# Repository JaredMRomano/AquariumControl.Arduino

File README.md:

# Aquarium Controller

Aquarium Controller a reef controller using Arduino and eventually Raspberri-Pi

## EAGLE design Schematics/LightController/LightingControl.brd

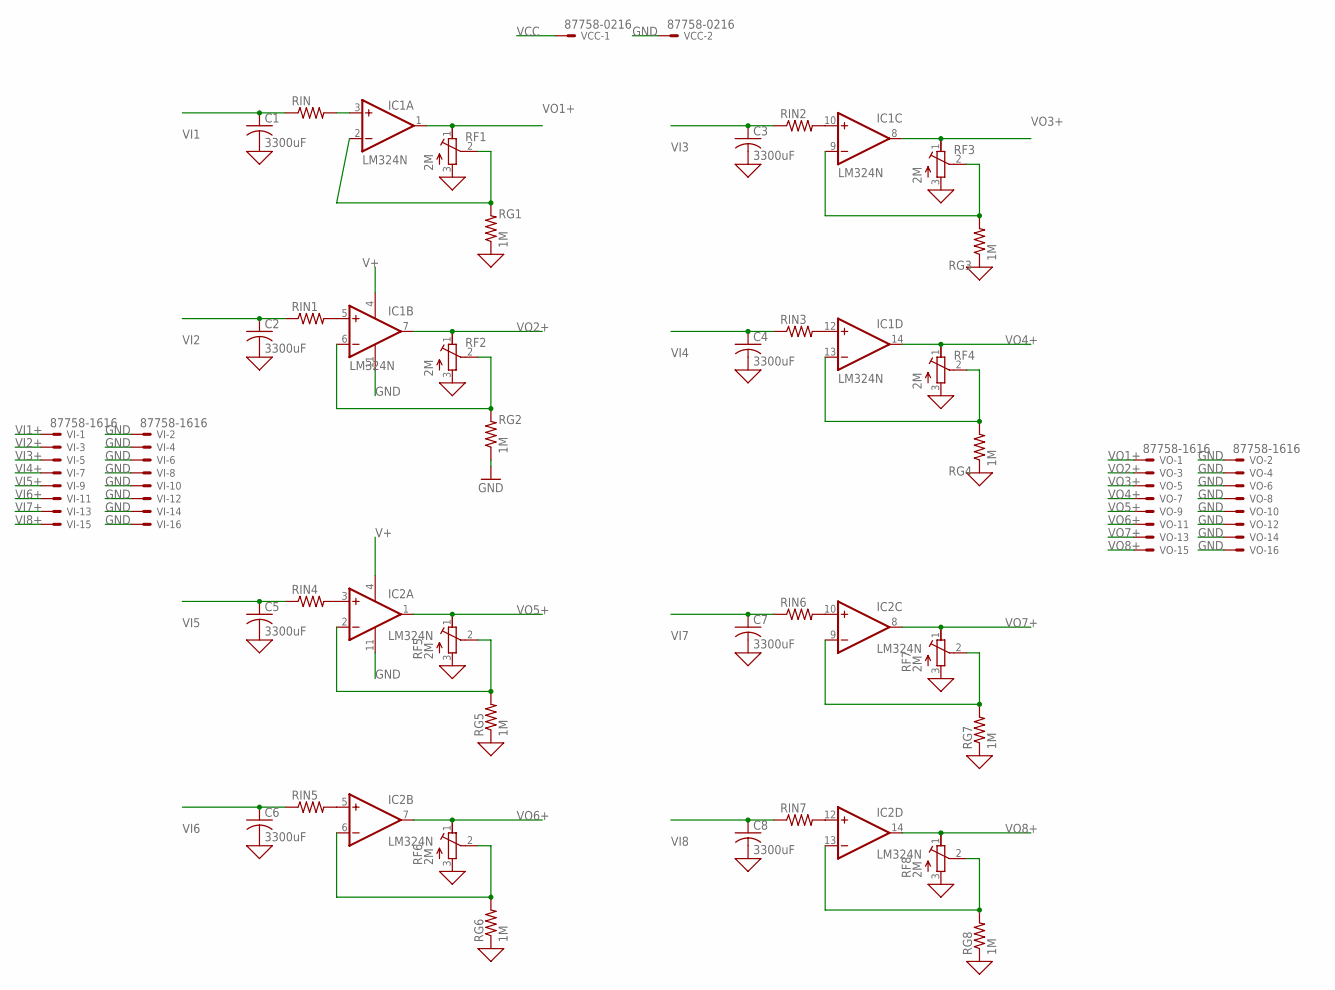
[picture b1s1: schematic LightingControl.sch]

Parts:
C1, C2, C3, C4, C5, C6, C7, C8: 3300uF; C025-024X044
IC1, IC2: LM324N; DIL14
RF1, RF2, RF3, RF4, RF5, RF6, RF7, RF8: 2M; RTRIM3314G
RG1, RG2, RG3, RG4, RG5, RG6, RG7, RG8: 1M; 0207/10
RIN, RIN1, RIN2, RIN3, RIN4, RIN5, RIN6, RIN7: R-US_0207/10; 0207/10
VCC: 87758-0216
VI: 87758-1616
VO: 87758-1616

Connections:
0: C1.2, C2.2, C3.2, C4.2, C5.2, C6.2, C7.2, C8.2, RF1.3 (A), RF2.3 (A), RF3.3 (A), RF4.3 (A), RF5.3 (A), RF6.3 (A), RF7.3 (A), RF8.3 (A), RG1.1, RG3.1, RG4.1, RG5.1, RG6.1, RG7.1, RG8.1
GND: IC1.11 (V-), IC2.11 (V-), RG2.1, VCC.2, VI.2, VI.4, VI.6, VI.8, VI.10, VI.12, VI.14, VI.16, VO.2, VO.4, VO.6, VO.8, VO.10, VO.12, VO.14, VO.16
unnamed: IC1.3 (+IN), RIN.2
unnamed: IC1.2 (-IN), RF1.2 (S), RG1.2
unnamed: IC1.6 (-IN), RF2.2 (S), RG2.2
unnamed: IC1.5 (+IN), RIN1.2
unnamed: IC1.9 (-IN), RF3.2 (S), RG3.2
unnamed: IC1.10 (+IN), RIN2.2
unnamed: IC1.13 (-IN), RF4.2 (S), RG4.2
unnamed: IC1.12 (+IN), RIN3.2
unnamed: IC2.2 (-IN), RF5.2 (S), RG5.2
unnamed: IC2.3 (+IN), RIN4.2
unnamed: IC2.6 (-IN), RF6.2 (S), RG6.2
unnamed: IC2.5 (+IN), RIN5.2
unnamed: IC2.9 (-IN), RF7.2 (S), RG7.2
unnamed: IC2.13 (-IN), RF8.2 (S), RG8.2
unnamed: IC2.10 (+IN), RIN6.2
unnamed: IC2.12 (+IN), RIN7.2
V+: IC1.4 (V+), IC2.4 (V+)
VCC: VCC.1
VI1: C1.1, RIN.1
VI1+: VI.1
VI2: C2.1, RIN1.1
VI2+: VI.3
VI3: C3.1, RIN2.1
VI3+: VI.5
VI4: C4.1, RIN3.1
VI4+: VI.7
VI5: C5.1, RIN4.1
VI5+: VI.9
VI6: C6.1, RIN5.1
VI6+: VI.11
VI7: C7.1, RIN6.1
VI7+: VI.13
VI8: C8.1, RIN7.1
VI8+: VI.15
VO1+: IC1.1 (OUT), RF1.1 (E), VO.1
VO2+: IC1.7 (OUT), RF2.1 (E), VO.3
VO3+: IC1.8 (OUT), RF3.1 (E), VO.5
VO4+: IC1.14 (OUT), RF4.1 (E), VO.7
VO5+: IC2.1 (OUT), RF5.1 (E), VO.9
VO6+: IC2.7 (OUT), RF6.1 (E), VO.11
VO7+: IC2.8 (OUT), RF7.1 (E), VO.13
VO8+: IC2.14 (OUT), RF8.1 (E), VO.15

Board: 2 copper layers, 37 parts (0 on the bottom side), 35 nets, no tracks yet.

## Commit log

2018-07-12 Added library directory to c_cpp_properties.json
2018-10-03 Added LightingControl Schematics
2018-10-05 updates to Light Schematics
2018-10-05 First pages commit
2018-10-05 first
2018-10-05 Revert "first"
    This reverts commit 7b07c856ce420e04e66ea504609f6a73b59c4e73.
2018-10-05 Revert "First pages commit"
    This reverts commit eeb04c5bcfebcbcc6bc6b643802c9bf44135c521.
2018-10-23 Added LightController Source Code
2018-10-26 Added RunTimeGroup Class
2018-11-06 Light dimmer working but needs tweaked
2018-12-27 Issue with start time. trying new design
2018-12-29 Full working
2019-09-25 REmoved bug: waiting for serial
